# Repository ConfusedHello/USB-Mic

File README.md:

# VOXMIC - A DIY Studio-Quality USB-C Microphone

[Film lights](https://github.com/ConfusedHello/Videography-Light/tree/main) shouldn't be so insanely expensive, but you know what else shouldn't be either? A quality microphone. VoxMic is a completely DIY mic I've designed for the Hack Club [Highway to Hardware](https://highway.hackclub.com/) program!

**QUICK WARNING: This WILL NOT WORK without the bodged fixes** [*more information here*](https://www.reddit.com/r/electronics/comments/1mqmphi/comment/n9i0p1c/?context=3)

This is definitely the largest project I've ever worked on - Version 1 along has gone though **6 entire revisions** just to get to where it is now. *V2 is in the works!!!*

For details about the design process or other information, check out the [development journal](https://highway.hackclub.com/projects/ConfusedHello/USB-Mic). A local copy is available in [JOURNAL.md](https://github.com/ConfusedHello/USB-Mic/blob/main/JOURNAL.md).

</img>

## The Design
Here's a quick diagram of the main components on the PCB~  

As well as the design for the PCB!  

And a quick image of the case-  
<details>
<summary>Click to expand/collapse</summary>

</details>

## Bill of Materials
Also available in .csv format in [BOM.csv](https://github.com/ConfusedHello/USB-Mic/blob/main/BOM.csv)!

|Item                   |Qty.|Price (USD)|Ext. (USD)|Link                                                                                                                              |
|-----------------------|----|-----------|----------|----------------------------------------------------------------------------------------------------------------------------------|
|C14663                 |100 |0.0024     |0.24      |https://lcsc.com/product-detail/multilayer-ceramic-capacitors-mlcc-smd-smt_yageo-cc0603krx7r9bb104_C14663.html                    |
|C21122                 |50  |0.0042     |0.21      |https://lcsc.com/product-detail/multilayer-ceramic-capacitors-mlcc-smd-smt_samsung-electro-mechanics-cl10b223kb8nnnc_C21122.html  |
|C22843                 |100 |0.0011     |0.11      |https://lcsc.com/product-detail/chip-resistor-surface-mount_uni-royal-uniroyal-elec-0603waf1501t5e_C22843.html                    |
|C23003                 |100 |0.0011     |0.11      |https://lcsc.com/product-detail/chip-resistor-surface-mount_uni-royal-uniroyal-elec-0603waf3322t5e_C23003.html                    |
|C28323                 |20  |0.0092     |0.18      |https://lcsc.com/product-detail/multilayer-ceramic-capacitors-mlcc-smd-smt_samsung-electro-mechanics-cl21b105kbfnnne_C28323.html  |
|C51205                 |10  |0.0337     |0.34      |https://lcsc.com/product-detail/multilayer-ceramic-capacitors-mlcc-smd-smt_samsung-electro-mechanics-cl31b475kbhnnne_C51205.html  |
|C59782                 |100 |0.005      |0.5       |https://lcsc.com/product-detail/multilayer-ceramic-capacitors-mlcc-smd-smt_samsung-electro-mechanics-cl10b105ko8nnnc_C59782.html  |
|C95841                 |10  |0.0232     |0.23      |https://lcsc.com/product-detail/multilayer-ceramic-capacitors-mlcc-smd-smt_samsung-electro-mechanics-cl21b106koqnnne_C95841.html  |
|C98220                 |100 |0.0011     |0.11      |https://lcsc.com/product-detail/chip-resistor-surface-mount_yageo-rc0603fr-0710kl_C98220.html                                     |
|C100042                |100 |0.0022     |0.22      |https://lcsc.com/product-detail/multilayer-ceramic-capacitors-mlcc-smd-smt_yageo-cc0603krx7r9bb103_C100042.html                   |
|C105578                |100 |0.0012     |0.12      |https://lcsc.com/product-detail/chip-resistor-surface-mount_yageo-rc0603fr-071ml_C105578.html                                     |
|C105620                |100 |0.0024     |0.24      |https://lcsc.com/product-detail/multilayer-ceramic-capacitors-mlcc-smd-smt_yageo-cc0603jrnpo9bn220_C105620.html                   |
|C108078                |100 |0.0012     |0.12      |https://lcsc.com/product-detail/chip-resistor-surface-mount_yageo-rc0603fr-073k3l_C108078.html                                    |
|C153298                |20  |0.0303     |0.61      |https://lcsc.com/product-detail/chip-resistor-surface-mount_ever-ohms-tech-tr0805b400rp0525z_C153298.html                         |
|C178482                |1   |0.3897     |0.39      |https://lcsc.com/product-detail/polypropylene-film-capacitors-cbb_panasonic-ecwfe2w225j_C178482.html                              |
|C180908                |1   |2.0425     |2.04      |https://lcsc.com/product-detail/voltage-regulators-linear-low-drop-out-ldo-regulators_texas-instruments-tps7a8901rtjr_C180908.html|
|C284149                |1   |4.8716     |4.87      |https://lcsc.com/product-detail/isolated-usb-ics_analog-devices-adum3160brwz-rl_C284149.html                                      |
|C309062                |4   |0.1383     |0.55      |https://lcsc.com/product-detail/multilayer-ceramic-capacitors-mlcc-smd-smt_samsung-electro-mechanics-cl32b226kajnnne_C309062.html |
|C454276                |2   |1.1425     |2.29      |https://lcsc.com/product-detail/polymer-aluminum-capacitors_panasonic-25svpk470m_C454276.html                                     |
|C475497                |1   |4.3489     |4.35      |https://lcsc.com/product-detail/audio-interface-ics_texas-instruments-pcm2912apjtr_C475497.html                                   |
|C541383                |100 |0.0011     |0.11      |https://lcsc.com/product-detail/multilayer-ceramic-capacitors-mlcc-smd-smt_yageo-cc0402krx7r8bb101_C541383.html                   |
|C596830                |5   |0.3215     |1.61      |https://lcsc.com/product-detail/crystals_abracon-llc-abls2-6-000mhz-d4y-t_C596830.html                                            |
|C668607                |5   |0.0783     |0.39      |https://lcsc.com/product-detail/audio-connectors_shou-han-pj-313-5jcj_C668607.html                                                |
|C965804                |100 |0.0044     |0.44      |https://lcsc.com/product-detail/led-indication-discrete_xinglight-xl-1608ugc-04_C965804.html                                      |
|C965807                |100 |0.0035     |0.35      |https://lcsc.com/product-detail/led-indication-discrete_xinglight-xl-1608ubc-04_C965807.html                                      |
|C2907018               |100 |0.0009     |0.09      |https://lcsc.com/product-detail/chip-resistor-surface-mount_fojan-frc0603f24r0ts_C2907018.html                                    |
|C2907044               |100 |0.001      |0.1       |https://lcsc.com/product-detail/chip-resistor-surface-mount_fojan-frc0603f5101ts_C2907044.html                                    |
|C2933225               |100 |0.001      |0.1       |https://lcsc.com/product-detail/chip-resistor-surface-mount_fojan-frc0603f4752ts_C2933225.html                                    |
|C2933510               |100 |0.0018     |0.18      |https://lcsc.com/product-detail/chip-resistor-surface-mount_fojan-frc0805f91r0ts_C2933510.html                                    |
|C2933610               |100 |0.0029     |0.29      |https://lcsc.com/product-detail/chip-resistor-surface-mount_fojan-frc1206f16r0ts_C2933610.html                                    |
|C2988369               |5   |0.0805     |0.4       |https://lcsc.com/product-detail/usb-connectors_g-switch-gt-usb-7010asv_C2988369.html                                              |
|C5153968               |100 |0.0009     |0.09      |https://lcsc.com/product-detail/chip-resistor-surface-mount_fojan-frc0603f1072ts_C5153968.html                                    |
|C7393948               |20  |0.022      |0.44      |https://lcsc.com/product-detail/multilayer-ceramic-capacitors-mlcc-smd-smt_cctc-tcc0805x7r335k250ft_C7393948.html                 |
|C7500927               |1   |1.2079     |1.21      |https://lcsc.com/product-detail/isolated-power-modules_evisun-b0505s-3wr2_C7500927.html                                           |
|C16197249              |5   |0.0579     |0.29      |https://lcsc.com/product-detail/power-inductors_yjycoin-yhnr4020-6r8m_C16197249.html                                              |
|LCSC Shipping          |1   |10.62      |10.62     |https://lcsc.com                                                                                                                  |
|CY018C                 |1   |30.00      |30.00     |https://www.alibaba.com/product-detail/797-Audio-CY018C-Custom-26mm-3um_1600884124178.html                                        |
|J305                   |1   |7.54       |7.54      |https://au.mouser.com/ProductDetail/InterFET/J305                                                                                 |
|MOX-400231007JE        |1   |10.29      |10.29     |https://au.mouser.com/ProductDetail/Ohmite/MOX-400231007JE                                                                        |
|Mouser Shipping        |1   |15.67      |15.67     |https://au.mouser.com                                                                                                             |
|JLCPCB Board           |1   |2.00       |2.00      |https://jlcpcb.com/                                                                                                               |
|JLCPCB Board Stencil   |1   |7.00       |7.00      |https://jlcpcb.com/                                                                                                               |
|JLCPCB Shipping        |1   |21.22      |21.22     |https://jlcpcb.com/                                                                                                               |
|Brass Tube             |1   |2.21       |2.21      |https://www.aliexpress.com/item/1005005239798226.html                                                                             |
|Brass Rod              |6   |12.52      |12.52     |https://www.aliexpress.com/item/1005008645247905.html                                                                             |
|2x100x200mm Brass Sheet|1   |17.38      |17.38     |https://www.aliexpress.com/item/1005007129408124.html                                                                             |
|Steel Mesh             |1   |2.80       |2.80      |https://www.aliexpress.com/item/1005003090693763.html                                                                             |
|Brass Wire             |1   |3.36       |3.36      |https://www.aliexpress.com/item/1005007182450013.html                                                                             |
|Wood Veneer            |1   |8.04       |8.04      |https://www.aliexpress.com/item/1005007643104919.html |

Total (USD): $174.57

## Notes for v2
- Capacitive touch button for muting
- Better status signalling to user
- Upgrade ADC/DAC

<hr>

Made with ❤️ by [@ConfusedHello](https://github.com/confusedhello)

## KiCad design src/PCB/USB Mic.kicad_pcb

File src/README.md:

Notes:

Get extra resistorrs for R11 and R12 to calibrate output
Get extra resistors for (cap biasing/supply)

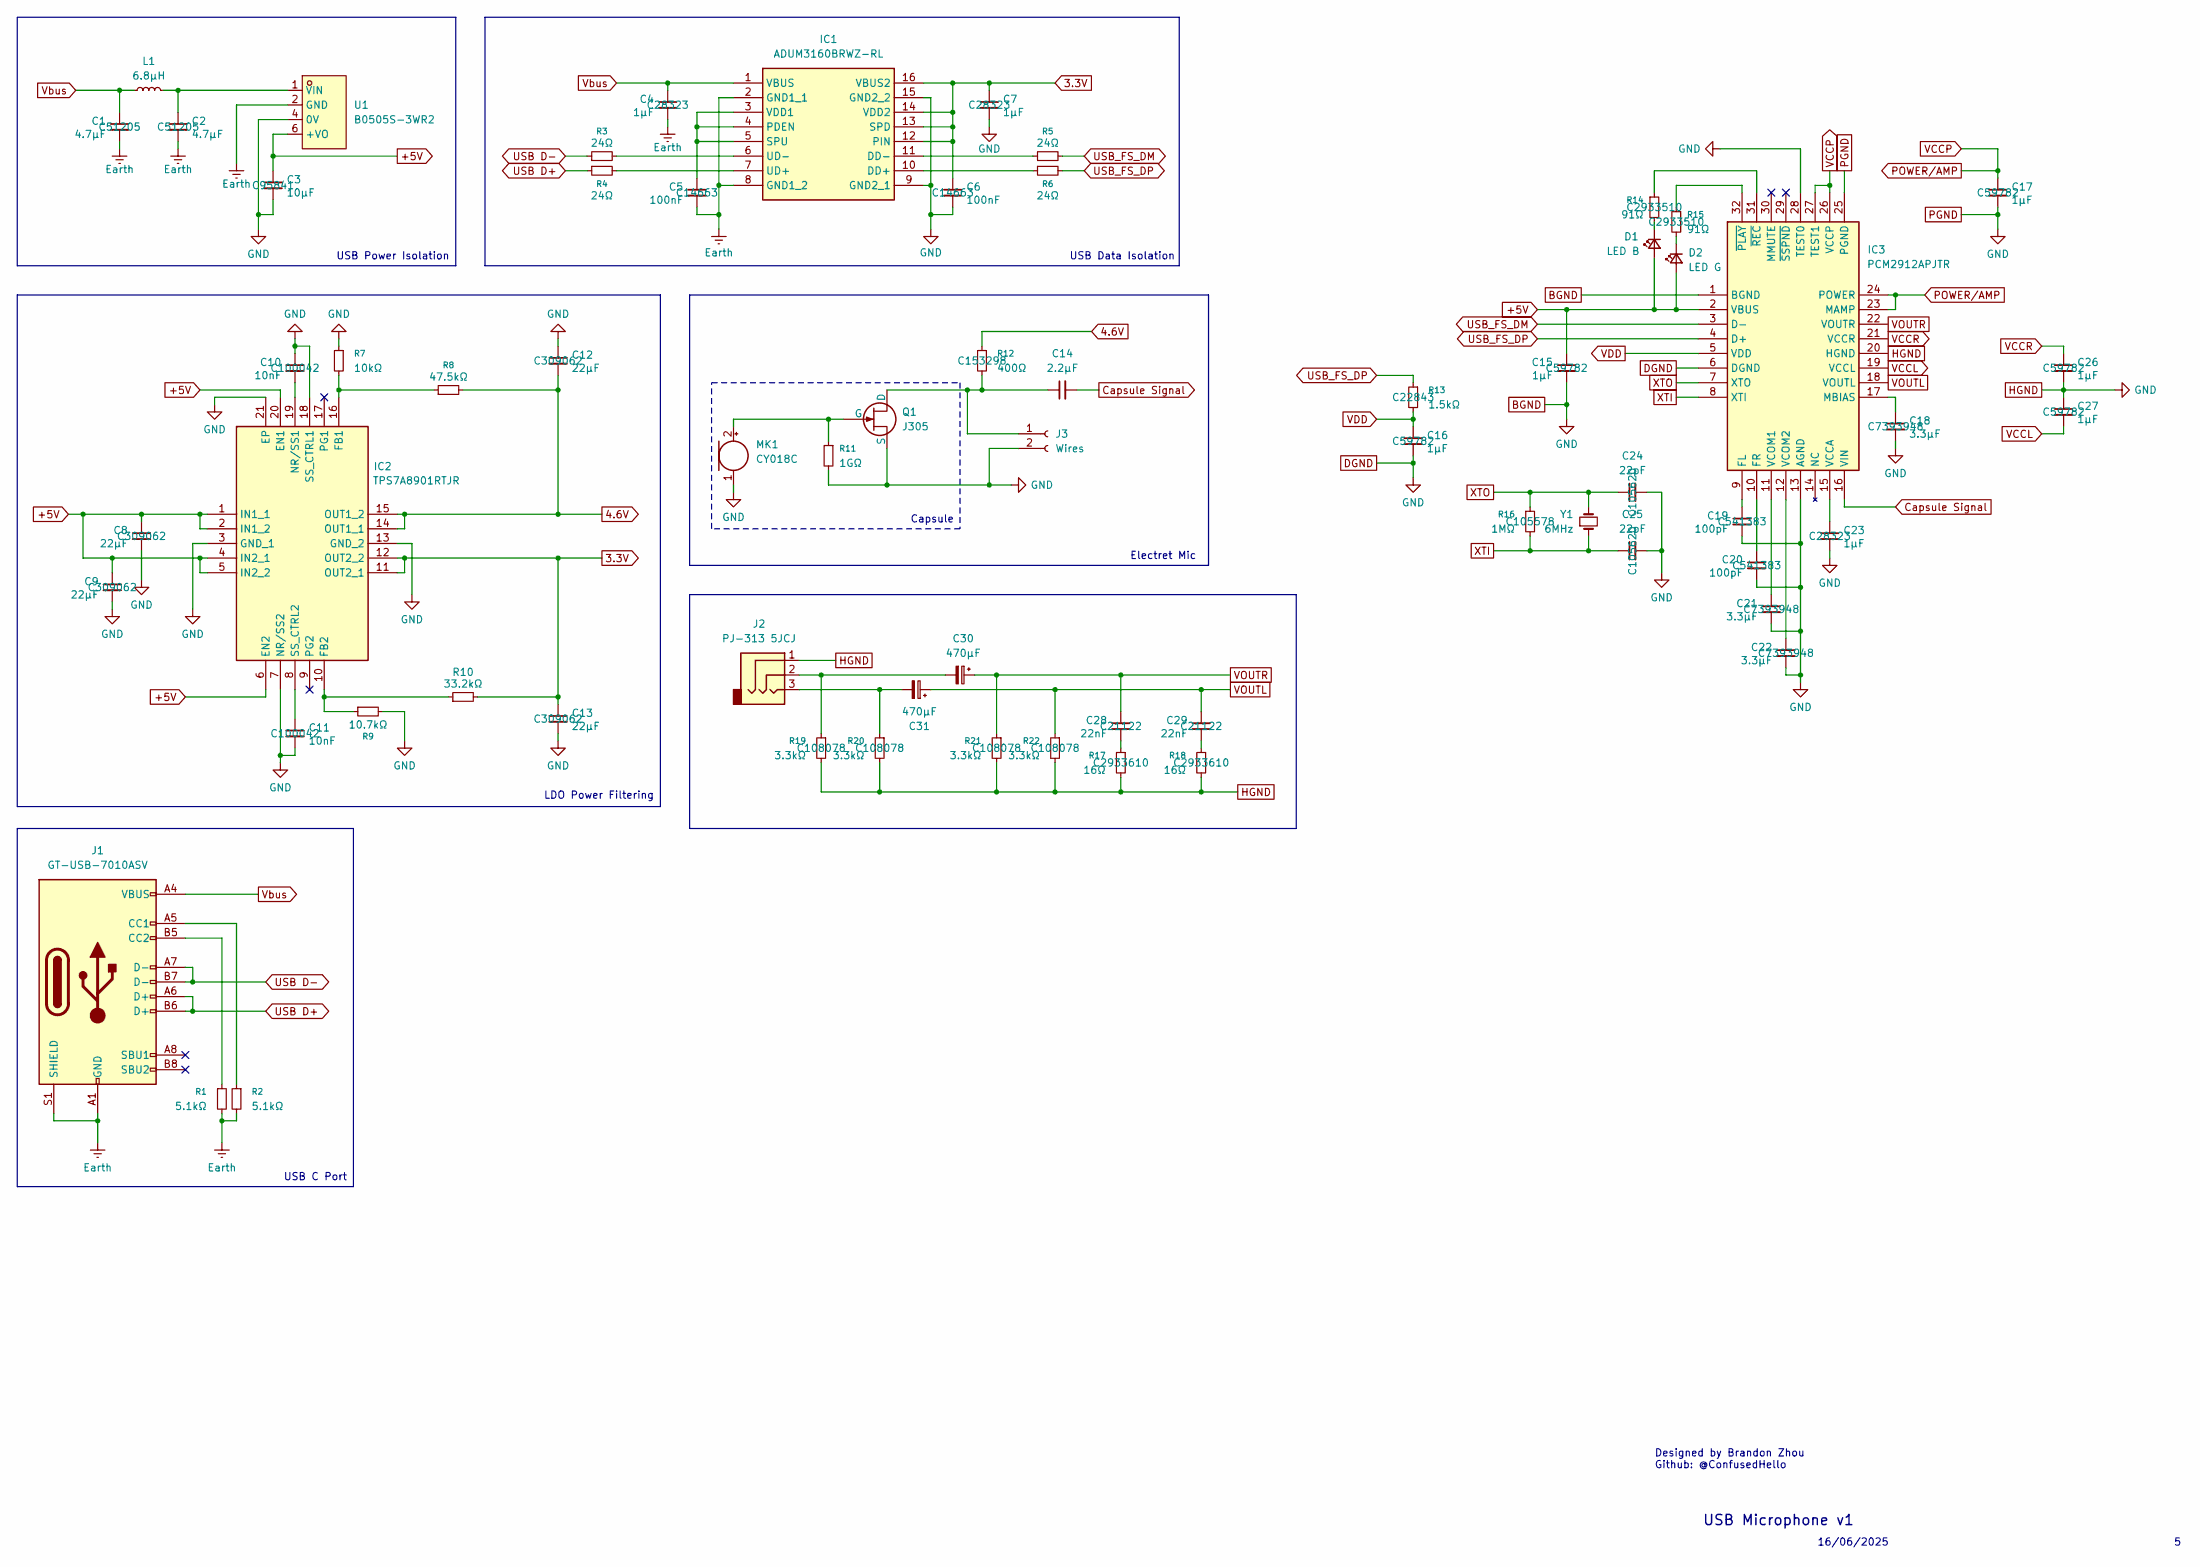
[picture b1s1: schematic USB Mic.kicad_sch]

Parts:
C1, C2: 4.7µF; C_1206_3216Metric_Pad1.33x1.80mm_HandSolder; LCSC C51205
C3: 10µF; C_0805_2012Metric_Pad1.18x1.45mm_HandSolder; LCSC C95841
C4, C7, C23: 1µF; C_0805_2012Metric_Pad1.18x1.45mm_HandSolder; LCSC C28323
C5, C6: 100nF; C_0603_1608Metric_Pad1.08x0.95mm_HandSolder; LCSC C14663
C8, C9, C12, C13: 22µF; C_1210_3225Metric_Pad1.33x2.70mm_HandSolder; LCSC C309062
C10, C11: 10nF; C_0603_1608Metric_Pad1.08x0.95mm_HandSolder; LCSC C100042
C14: 2.2µF; CAP-TH_L17.5-W10.0-P15.00-D1.2; LCSC C178482
C15, C16, C17, C26, C27: 1µF; C_0603_1608Metric_Pad1.08x0.95mm_HandSolder; LCSC C59782
C18, C21, C22: 3.3µF; C_0805_2012Metric_Pad1.18x1.45mm_HandSolder; LCSC C7393948
C19, C20: 100pF; C_0402_1005Metric_Pad0.74x0.62mm_HandSolder; LCSC C541383
C24, C25: 22pF; C_0603_1608Metric_Pad1.08x0.95mm_HandSolder; LCSC C105620
C28, C29: 22nF; C_0603_1608Metric_Pad1.08x0.95mm_HandSolder; LCSC C21122
C30, C31: 470µF; CAP-SMD_BD10.0-L10.3-W10.3-LS11.0-FD-1; LCSC C454276
D1: LED B; LED_0603_1608Metric_Pad1.05x0.95mm_HandSolder; LCSC C965807
D2: LED G; LED_0603_1608Metric_Pad1.05x0.95mm_HandSolder; LCSC C965804
IC1: ADUM3160BRWZ-RL; SOIC127P1032X265-16N; Manufacturer_Part_Number ADUM3160BRWZ-RL; LCSC C284149
IC2: TPS7A8901RTJR; QFN50P400X400X80-21N-D; Manufacturer_Part_Number TPS7A8901RTJR; LCSC C180908
IC3: PCM2912APJTR; QFP80P900X900X120-32N; Manufacturer_Part_Number PCM2912APJTR; LCSC C475497
J1: GT-USB-7010ASV; USB_C_Receptacle_G-Switch_GT-USB-7010ASV; LCSC C2988369
J2: PJ-313 5JCJ; AUDIO-TH_PJ-313_5JCJ; LCSC C668607
J3: Wires; SolderWire-0.1sqmm_1x02_P3.6mm_D0.4mm_OD1mm
L1: 6.8µH; IND-SMD_L4.0-W4.0_YHNR4020; LCSC C16197249
MK1: CY018C
Q1: J305
R1, R2: 5.1kΩ; R_0603_1608Metric_Pad0.98x0.95mm_HandSolder; LCSC C2907044
R3, R4, R5, R6: 24Ω; R_0603_1608Metric_Pad0.98x0.95mm_HandSolder; LCSC C2907018
R7: 10kΩ; R_0603_1608Metric_Pad0.98x0.95mm_HandSolder; LCSC C98220
R8: 47.5kΩ; R_0603_1608Metric_Pad0.98x0.95mm_HandSolder; LCSC C2933225
R9: 10.7kΩ; R_0603_1608Metric_Pad0.98x0.95mm_HandSolder; LCSC C5153968
R10: 33.2kΩ; R_0603_1608Metric_Pad0.98x0.95mm_HandSolder; LCSC C23003
R11: 1GΩ
R12: 400Ω; R_0805_2012Metric_Pad1.20x1.40mm_HandSolder; LCSC C153298
R13: 1.5kΩ; R_0603_1608Metric_Pad0.98x0.95mm_HandSolder; LCSC C22843
R14, R15: 91Ω; R_0805_2012Metric_Pad1.20x1.40mm_HandSolder; LCSC C2933510
R16: 1MΩ; R_0603_1608Metric_Pad0.98x0.95mm_HandSolder; LCSC C105578
R17, R18: 16Ω; R_1206_3216Metric_Pad1.30x1.75mm_HandSolder; LCSC C2933610
R19, R20, R21, R22: 3.3kΩ; R_0603_1608Metric_Pad0.98x0.95mm_HandSolder; LCSC C108078
U1: B0505S-3WR2; LCSC C7500927
Y1: 6MHz; ABLS; LCSC C596830

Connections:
3.3V: C6.1, C7.1, C13.1, IC1.12 (PIN), IC1.13 (SPD), IC1.14 (VDD2), IC1.16 (VBUS2), IC2.11 (OUT2_1), IC2.12 (OUT2_2), R10.2
4.6V: C12.2, IC2.14 (OUT1_1), IC2.15 (OUT1_2), R8.2, R12.1
+5V: C3.1, C8.1, C9.1, C15.1, D1.2 (A), D2.2 (A), IC2.1 (IN1_1), IC2.2 (IN1_2), IC2.4 (IN2_1), IC2.5 (IN2_2), IC2.6 (EN2), IC2.20 (EN1), IC3.2 (VBUS), U1.6 (+VO)
BGND: C3.2, C6.2, C7.2, C8.2, C9.2, C10.1, C11.2, C12.1, C13.2, C15.2, C16.2, C17.2, C18.2, C19.2, C20.2, C21.2, C22.2, C23.2, C24.2, C25.2, C26.2, C27.1, IC1.9 (GND2_1), IC1.15 (GND2_2), IC2.3 (GND_1), IC2.7 (NR/SS2), IC2.13 (GND_2), IC2.18 (SS_CTRL1), IC2.21 (EP), IC3.1 (BGND), IC3.6 (DGND), IC3.13 (AGND), IC3.20 (HGND), IC3.25 (PGND), IC3.28 (TEST0), J2.1, J3.2, MK1.1 (-), Q1.3 (S), R7.1, R9.2, R11.2, R17.2, R18.2, R19.2, R20.2, R21.2, R22.2, U1.4 (0V)
Capsule Signal: C14.2, IC3.16 (VIN)
Earth: C1.2, C2.2, C4.2, C5.2, IC1.2 (GND1_1), IC1.8 (GND1_2), J1.A1 (GND), J1.A12 (GND), J1.B1 (GND), J1.B12 (GND), J1.S1 (SHIELD), R1.2, R2.2, U1.2 (GND)
unnamed: C28.2, R17.1
unnamed: C29.2, R18.1
unnamed: C30.2, J2.2, R19.1
unnamed: C31.2, J2.3, R20.1
unnamed: D1.1 (K), R14.2
unnamed: D2.1 (K), R15.2
unnamed: IC1.10 (DD+), R6.1
unnamed: IC1.11 (DD-), R5.1
unnamed: C5.1, IC1.3 (VDD1), IC1.4 (PDEN), IC1.5 (SPU)
unnamed: IC1.7 (UD+), R4.2
unnamed: IC1.6 (UD-), R3.2
unnamed: IC2.16 (FB1), R7.2, R8.1
unnamed: IC2.10 (FB2), R9.1, R10.1
unnamed: C10.2, IC2.19 (NR/SS1)
unnamed: C11.1, IC2.8 (SS_CTRL2)
unnamed: C19.1, IC3.9 (FL)
unnamed: C20.1, IC3.10 (FR)
unnamed: C18.1, IC3.17 (MBIAS)
unnamed: C23.1, IC3.15 (VCCA)
unnamed: C21.1, IC3.11 (VCOM1)
unnamed: C22.1, IC3.12 (VCOM2)
unnamed: IC3.32 (~PLAY), R15.1
unnamed: IC3.31 (~REC), R14.1
unnamed: J1.A5 (CC1), R2.1
unnamed: J1.B5 (CC2), R1.1
unnamed: C14.1, J3.1, Q1.1 (D), R12.2
unnamed: MK1.2 (+), Q1.2 (G), R11.1
unnamed: C2.1, L1.2, U1.1 (VIN)
POWER/AMP: C17.1, IC3.23 (MAMP), IC3.24 (POWER), IC3.26 (VCCP), IC3.27 (TEST1)
USB D+: J1.A6 (D+), J1.B6 (D+), R4.1
USB D-: J1.A7 (D-), J1.B7 (D-), R3.1
USB_FS_DM: IC3.3 (D-), R5.2
USB_FS_DP: IC3.4 (D+), R6.2, R13.1
VCCL: C27.2, IC3.19 (VCCL)
VCCR: C26.1, IC3.21 (VCCR)
VDD: C16.1, IC3.5 (VDD), R13.2
VOUTL: C29.1, C31.1, IC3.18 (VOUTL), R22.1
VOUTR: C28.1, C30.1, IC3.22 (VOUTR), R21.1
Vbus: C1.1, C4.1, IC1.1 (VBUS), J1.A4 (VBUS), J1.A9 (VBUS), J1.B4 (VBUS), J1.B9 (VBUS), L1.1
XTI: C25.1, IC3.8 (XTI), R16.2, Y1.1
XTO: C24.1, IC3.7 (XTO), R16.1, Y1.2

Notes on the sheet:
Electret Mic
Designed by Brandon Zhou Github: @ConfusedHello
USB C Port
USB Microphone v1
USB Power Isolation
16/06/2025
LDO Power Filtering
USB Data Isolation
Capsule

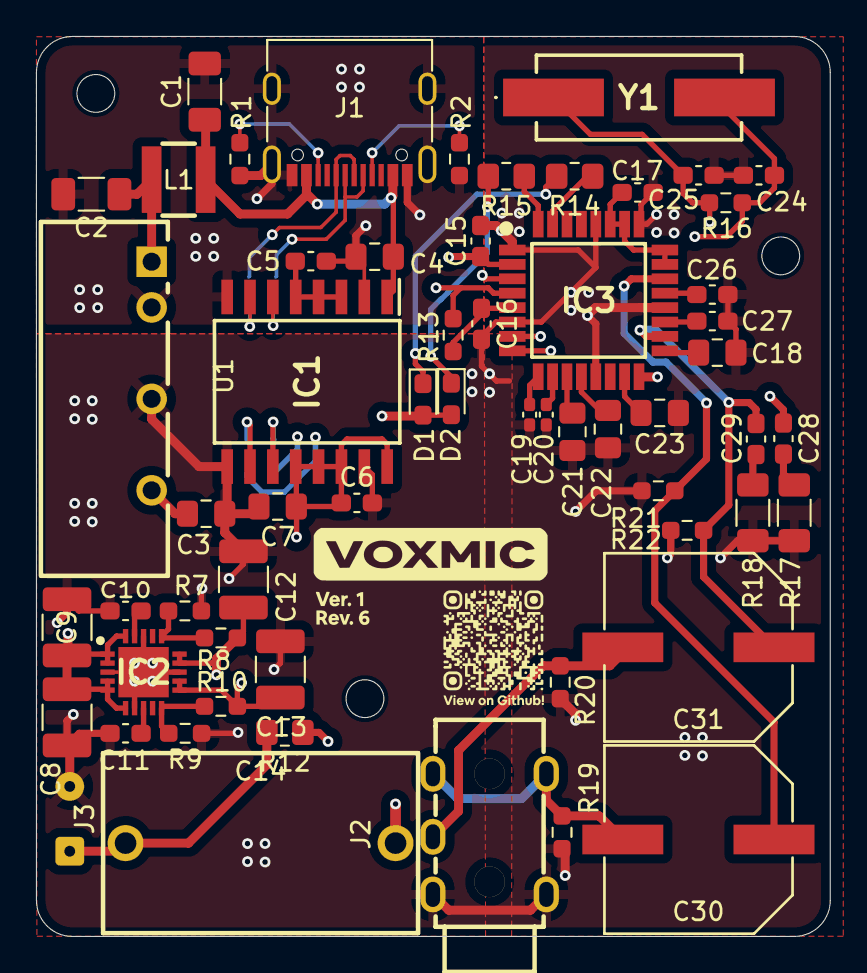
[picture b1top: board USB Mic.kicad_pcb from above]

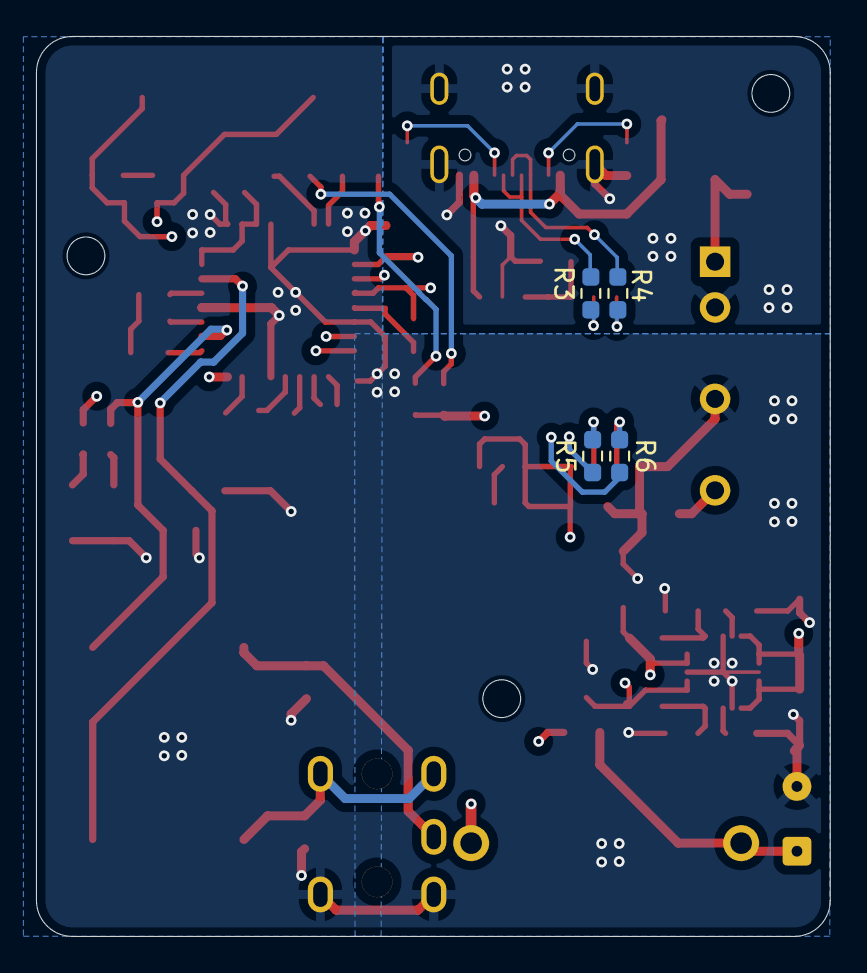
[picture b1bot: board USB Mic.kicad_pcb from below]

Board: 4 copper layers, 44.1 x 50.0 mm, 63 parts (4 on the bottom side), 46 nets.

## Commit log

2025-06-10 Update JOURNAL
2025-06-12 Add .gitignore for KiCad
2025-06-12 Upload Rev. 4 Schematic
2025-06-13 Update Rev.4 Schematic
2025-06-18 Upload SPICE and update schematic
2025-06-19 Fix image display on Highway website
2025-06-20 Update to Rev. 5
2025-07-09 Upload 3D Models
2025-07-09 Finalise PCB
2025-07-09 Update README and JOURNAL to prepare for submission
2025-07-09 Fix BOM
2025-07-09 Add sneak peak to JOURNAL
2025-07-10 Upload KiCad 3D model
2025-07-12 Push images
2025-07-19 Cleanup for submission
2025-07-19 Fix KiCad .csv gitignore issue
2025-07-19 Upload BOM files
2025-07-19 Fix README <details>
